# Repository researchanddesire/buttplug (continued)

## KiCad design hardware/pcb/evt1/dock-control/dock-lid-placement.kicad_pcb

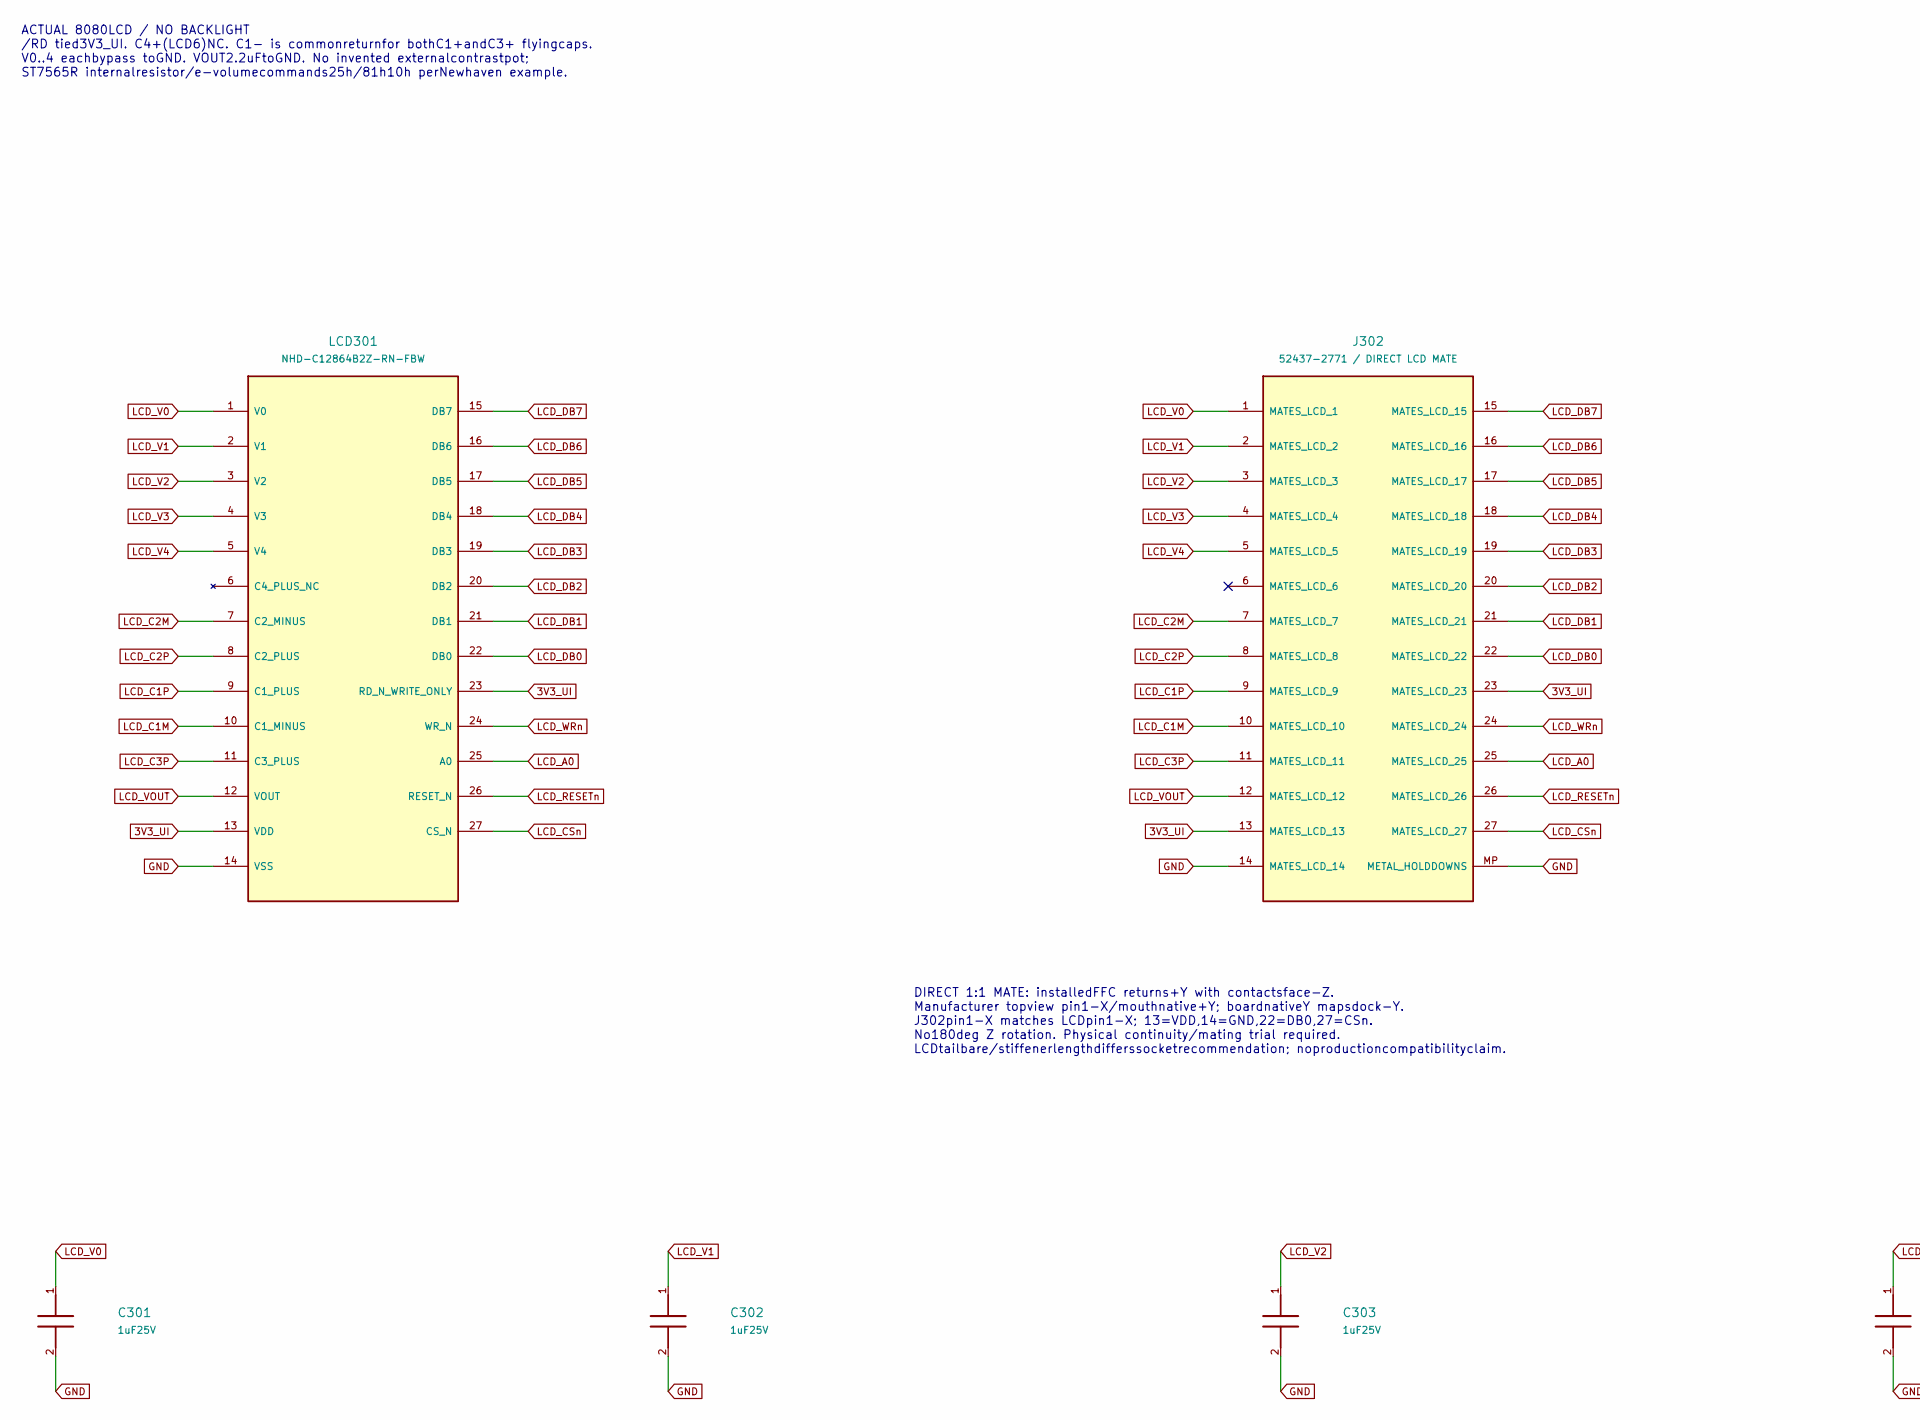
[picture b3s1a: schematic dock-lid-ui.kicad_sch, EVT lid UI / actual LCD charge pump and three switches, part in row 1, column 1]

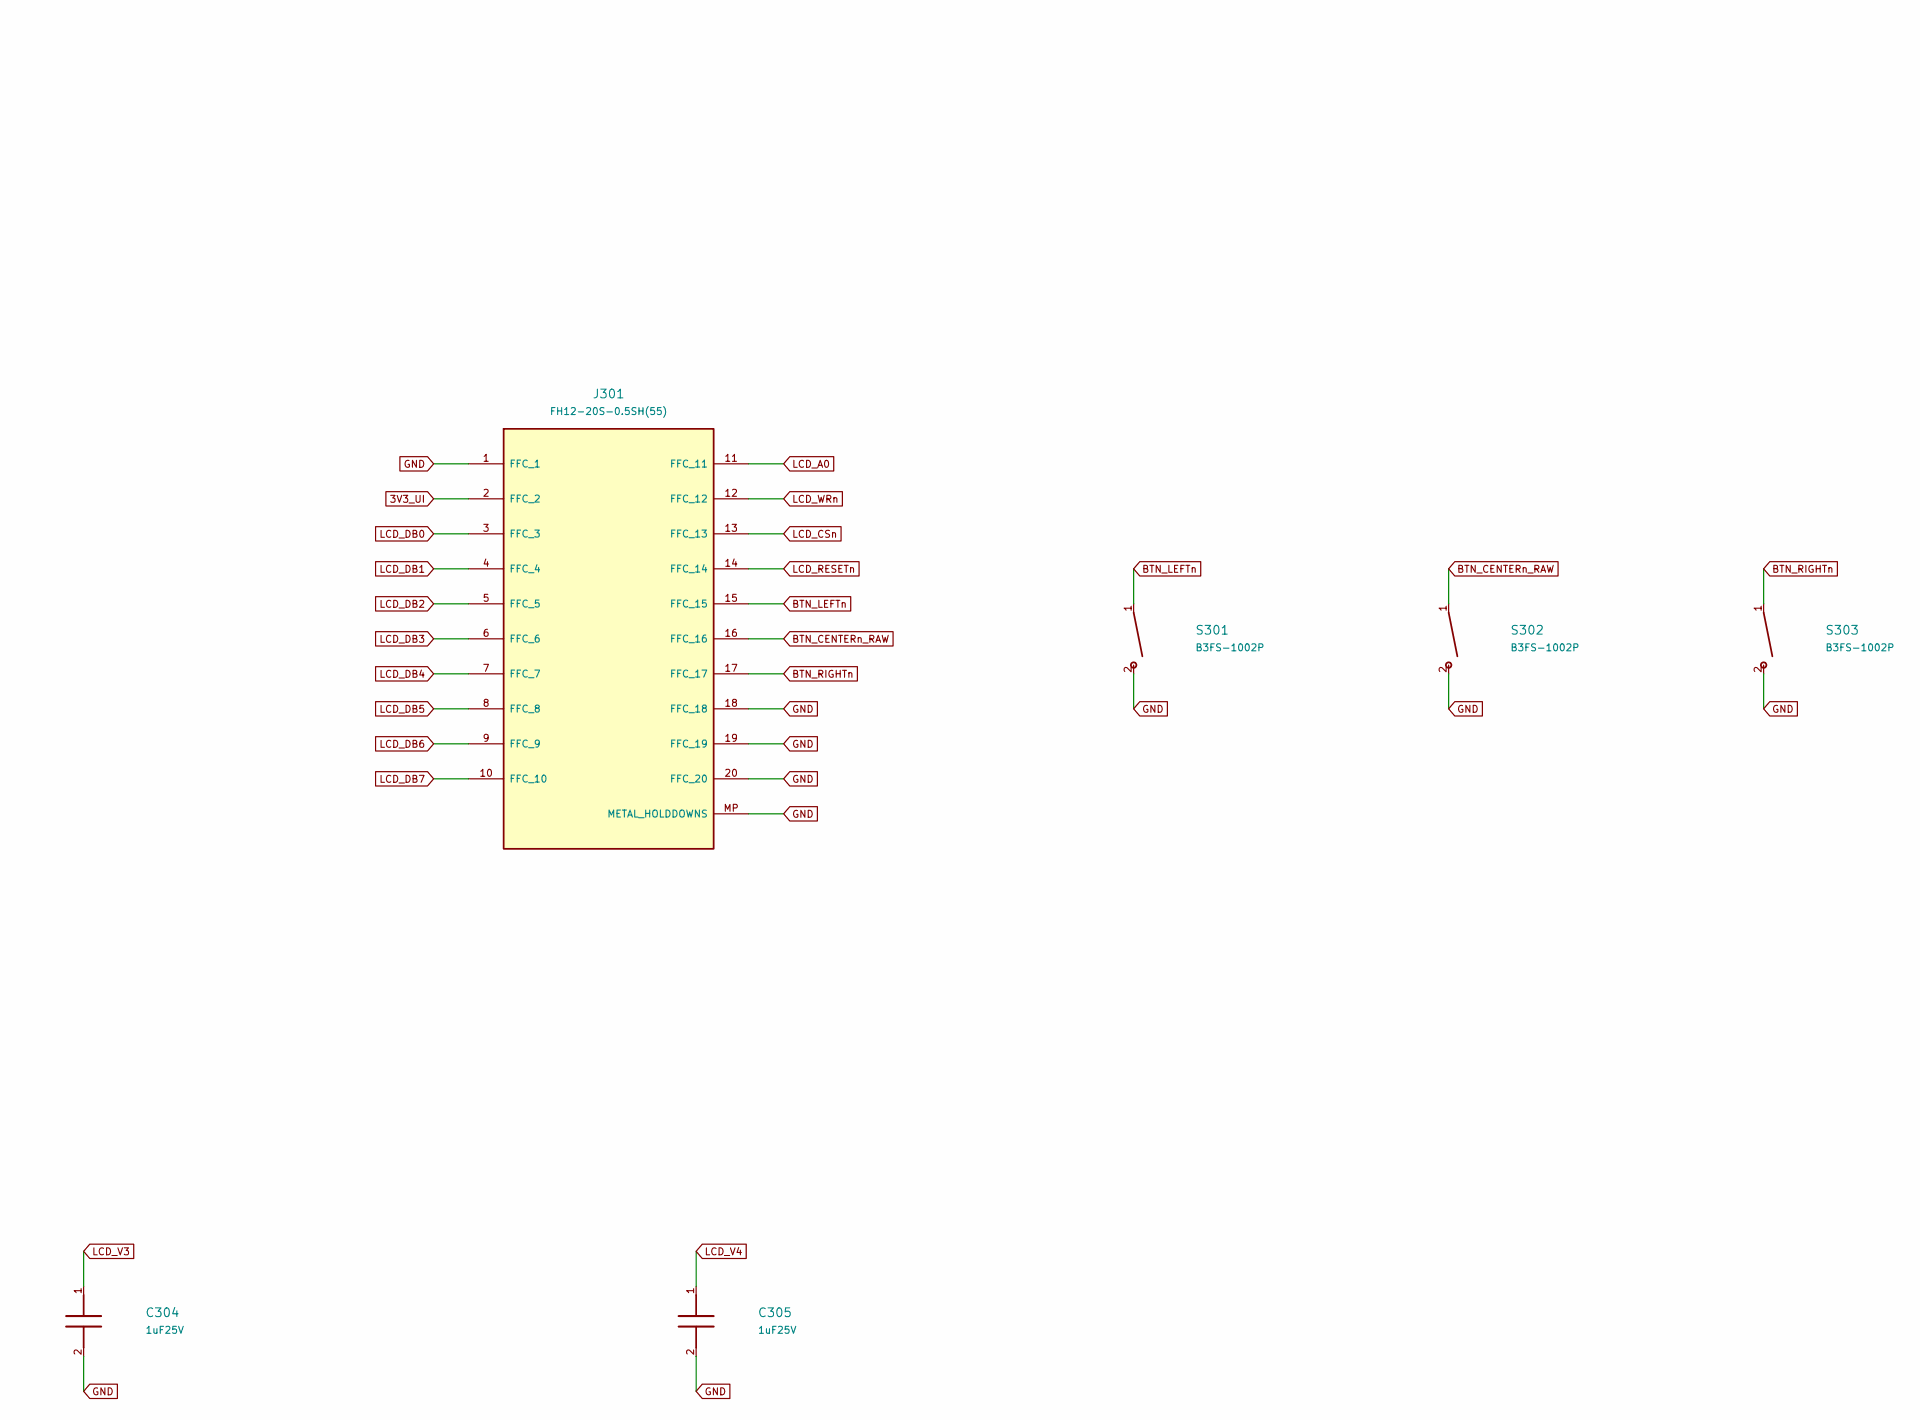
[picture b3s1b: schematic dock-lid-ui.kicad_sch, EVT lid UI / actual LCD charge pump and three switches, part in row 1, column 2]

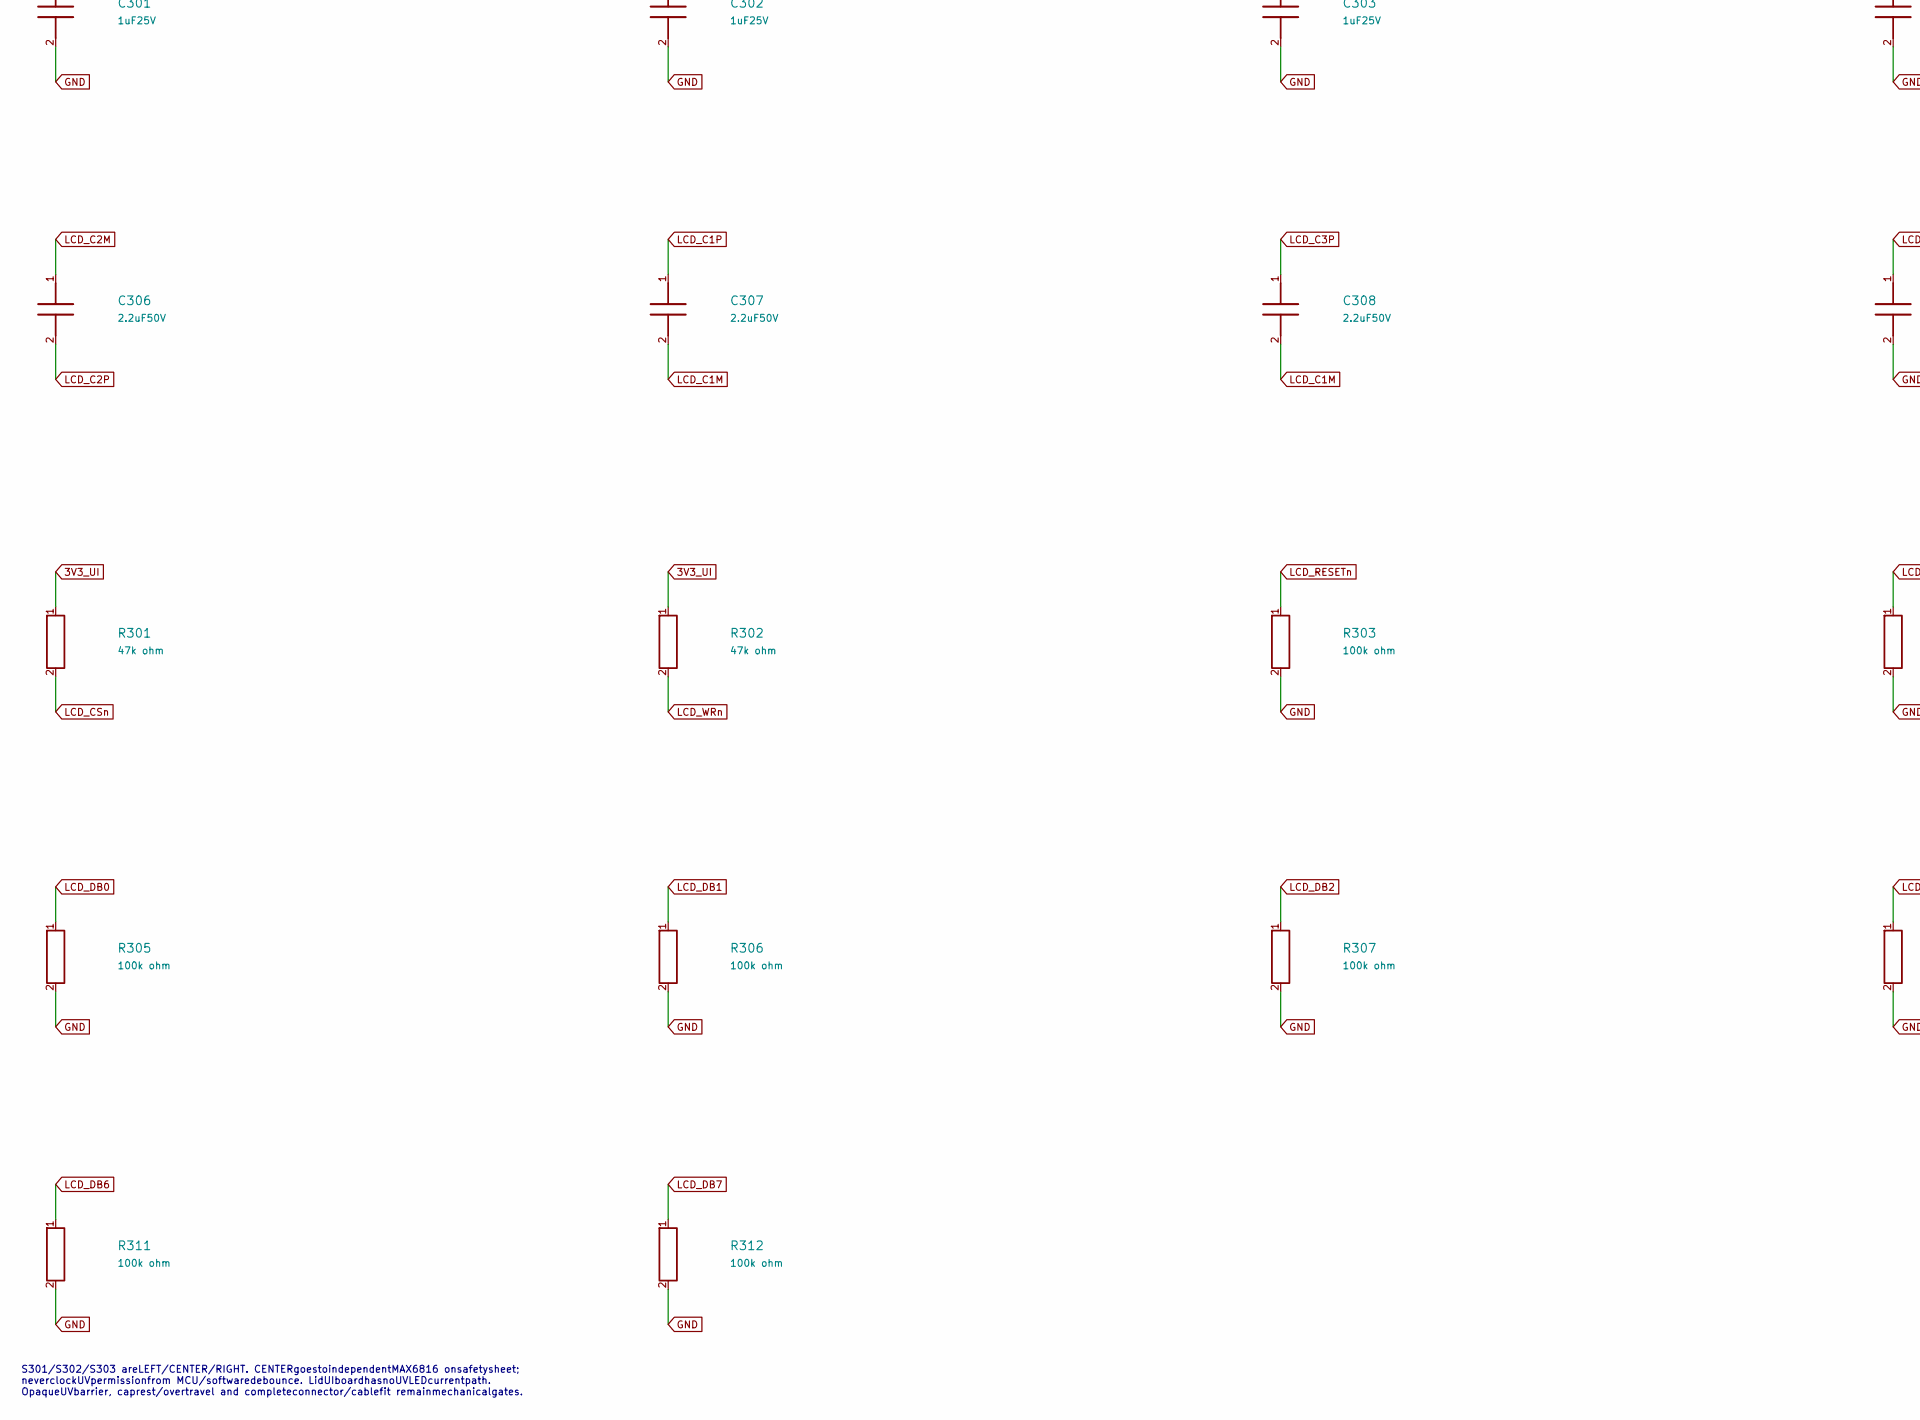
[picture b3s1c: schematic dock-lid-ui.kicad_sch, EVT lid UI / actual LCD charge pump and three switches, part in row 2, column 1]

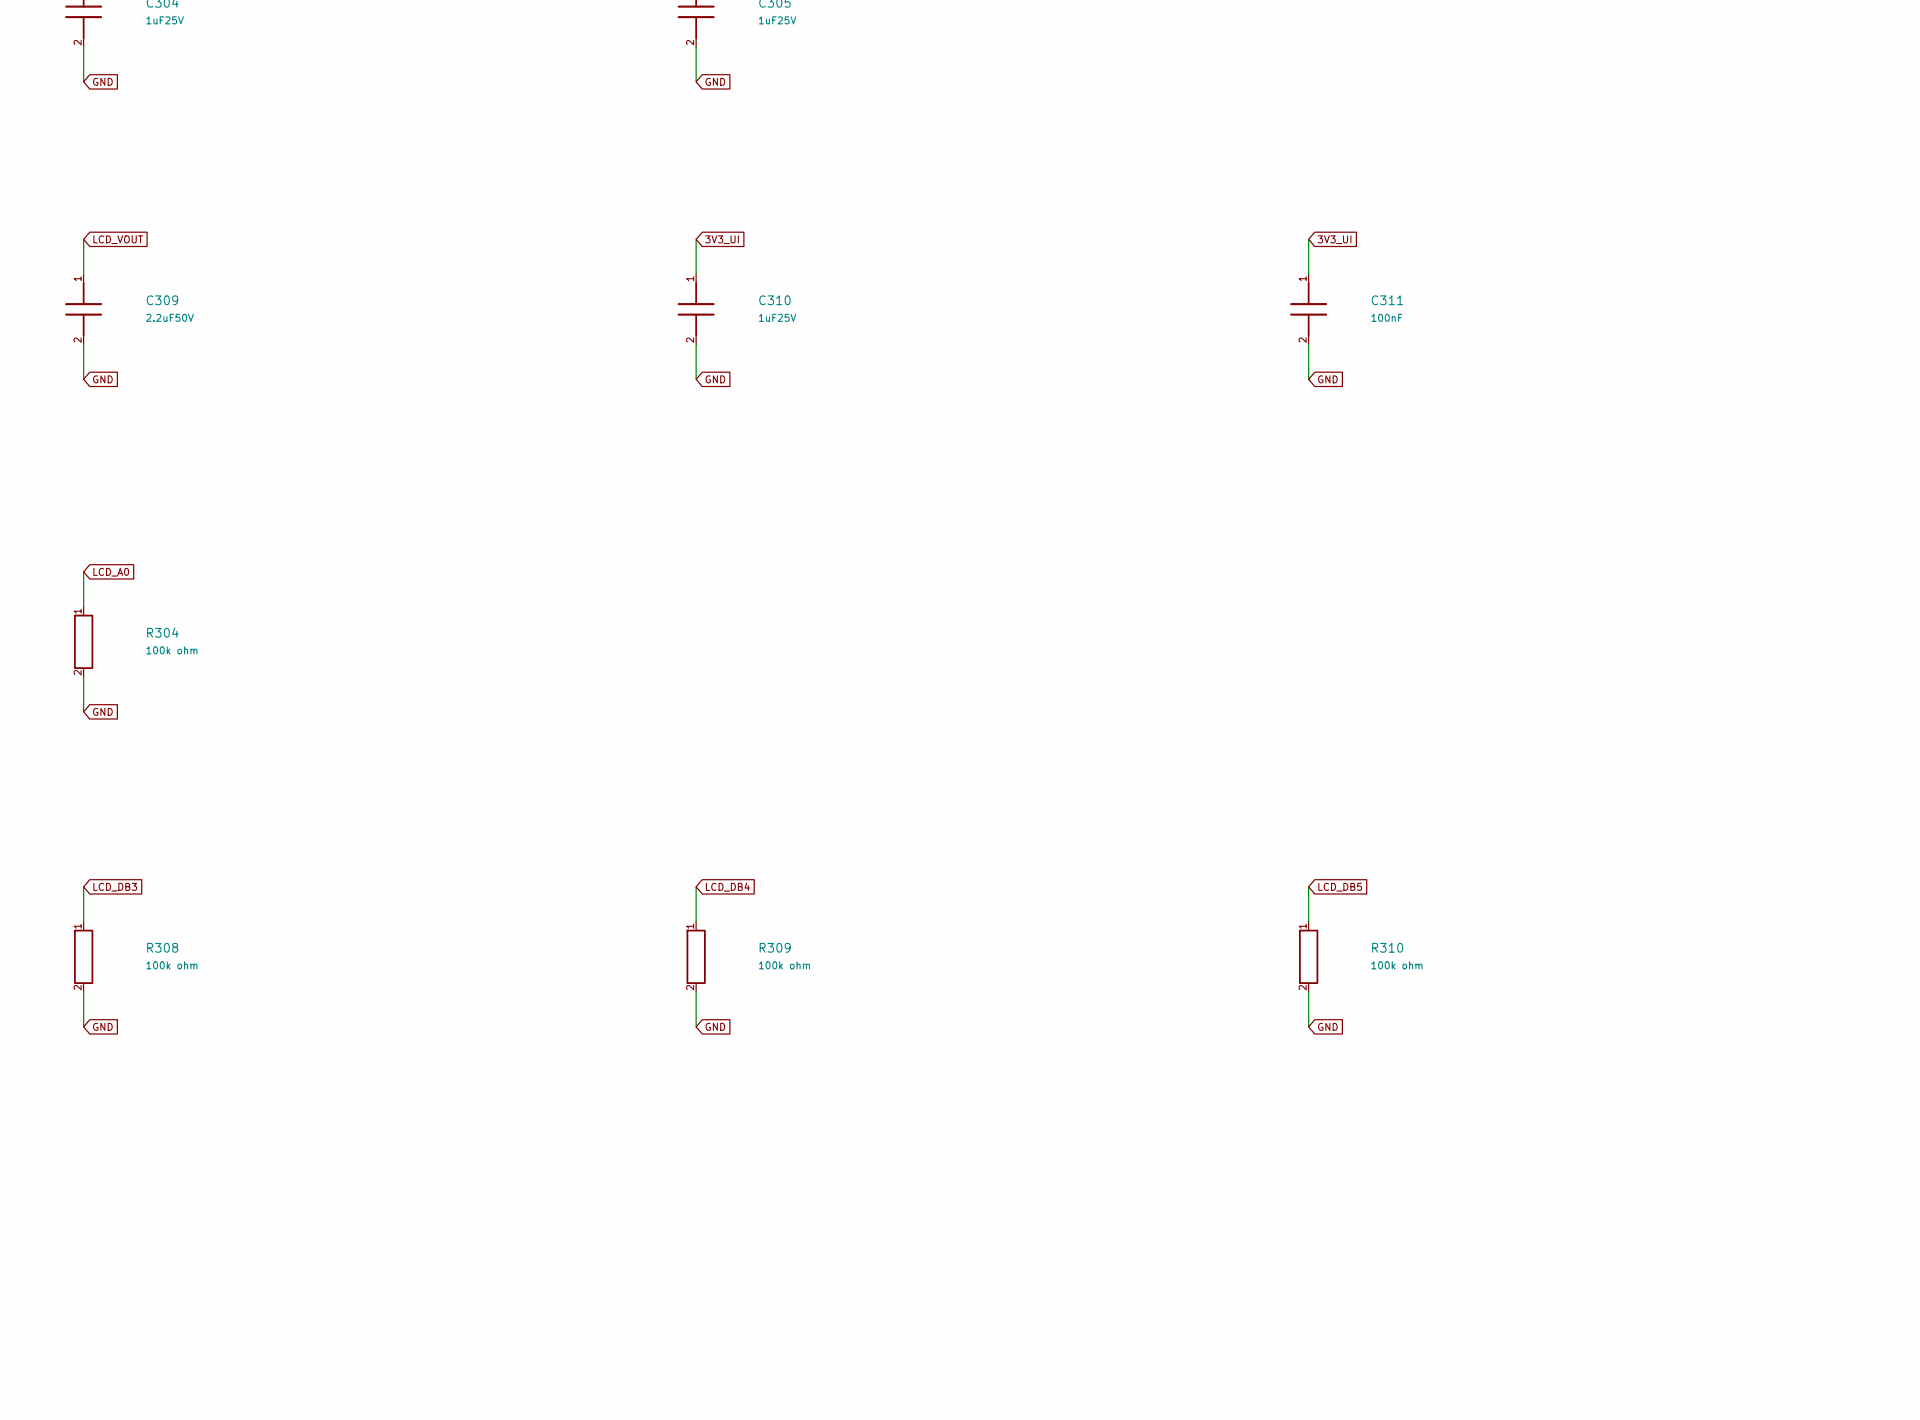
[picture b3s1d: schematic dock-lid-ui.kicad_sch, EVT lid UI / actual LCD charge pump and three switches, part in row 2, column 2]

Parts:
C301, C302, C303, C304, C305, C310: 1uF25V; C_0603_1608Metric; MPN C1608X7R1E105K080AB
C306, C307, C308, C309: 2.2uF50V; C_1206_3216Metric; MPN C3216X7R1H225K160AB
C311: 100nF; C_0402_1005Metric; MPN GRM155R71C104KA88D
J301: FH12-20S-0.5SH(55); Hirose_FH12-20S-0.5SH_1x20-1MP_P0.50mm_Horizontal; MPN FH12-20S-0.5SH(55)
J302: 52437-2771 / DIRECT LCD MATE; Molex_52437-2771_1x27-1MP_P0.50mm_Horizontal; MPN 52437-2771
LCD301: NHD-C12864B2Z-RN-FBW; MPN NHD-C12864B2Z-RN-FBW
R301, R302: 47k ohm; R_0603_1608Metric; MPN RC0603FR-0747KL
R303, R304, R305, R306, R307, R308, R309, R310, R311, R312: 100k ohm; R_0603_1608Metric; MPN RC0603FR-07100KL
S301, S302, S303: B3FS-1002P; SW_SPST_Omron_B3FS-100xP; MPN B3FS-1002P

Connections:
3V3_UI: C310.1, C311.1, J301.2 (FFC_2), J302.13 (MATES_LCD_13), J302.23 (MATES_LCD_23), LCD301.13 (VDD), LCD301.23 (RD_N_WRITE_ONLY), R301.1, R302.1
BTN_CENTERn_RAW: J301.16 (FFC_16), S302.1
BTN_LEFTn: J301.15 (FFC_15), S301.1
BTN_RIGHTn: J301.17 (FFC_17), S303.1
GND: C301.2, C302.2, C303.2, C304.2, C305.2, C309.2, C310.2, C311.2, J301.1 (FFC_1), J301.18 (FFC_18), J301.19 (FFC_19), J301.20 (FFC_20), J301.MP (METAL_HOLDDOWNS), J302.14 (MATES_LCD_14), J302.MP (METAL_HOLDDOWNS), LCD301.14 (VSS), R303.2, R304.2, R305.2, R306.2, R307.2, R308.2, R309.2, R310.2, R311.2, R312.2, S301.2, S302.2, S303.2
LCD_A0: J301.11 (FFC_11), J302.25 (MATES_LCD_25), LCD301.25 (A0), R304.1
LCD_C1M: C307.2, C308.2, J302.10 (MATES_LCD_10), LCD301.10 (C1_MINUS)
LCD_C1P: C307.1, J302.9 (MATES_LCD_9), LCD301.9 (C1_PLUS)
LCD_C2M: C306.1, J302.7 (MATES_LCD_7), LCD301.7 (C2_MINUS)
LCD_C2P: C306.2, J302.8 (MATES_LCD_8), LCD301.8 (C2_PLUS)
LCD_C3P: C308.1, J302.11 (MATES_LCD_11), LCD301.11 (C3_PLUS)
LCD_CSn: J301.13 (FFC_13), J302.27 (MATES_LCD_27), LCD301.27 (CS_N), R301.2
LCD_DB0: J301.3 (FFC_3), J302.22 (MATES_LCD_22), LCD301.22 (DB0), R305.1
LCD_DB1: J301.4 (FFC_4), J302.21 (MATES_LCD_21), LCD301.21 (DB1), R306.1
LCD_DB2: J301.5 (FFC_5), J302.20 (MATES_LCD_20), LCD301.20 (DB2), R307.1
LCD_DB3: J301.6 (FFC_6), J302.19 (MATES_LCD_19), LCD301.19 (DB3), R308.1
LCD_DB4: J301.7 (FFC_7), J302.18 (MATES_LCD_18), LCD301.18 (DB4), R309.1
LCD_DB5: J301.8 (FFC_8), J302.17 (MATES_LCD_17), LCD301.17 (DB5), R310.1
LCD_DB6: J301.9 (FFC_9), J302.16 (MATES_LCD_16), LCD301.16 (DB6), R311.1
LCD_DB7: J301.10 (FFC_10), J302.15 (MATES_LCD_15), LCD301.15 (DB7), R312.1
LCD_RESETn: J301.14 (FFC_14), J302.26 (MATES_LCD_26), LCD301.26 (RESET_N), R303.1
LCD_V0: C301.1, J302.1 (MATES_LCD_1), LCD301.1 (V0)
LCD_V1: C302.1, J302.2 (MATES_LCD_2), LCD301.2 (V1)
LCD_V2: C303.1, J302.3 (MATES_LCD_3), LCD301.3 (V2)
LCD_V3: C304.1, J302.4 (MATES_LCD_4), LCD301.4 (V3)
LCD_V4: C305.1, J302.5 (MATES_LCD_5), LCD301.5 (V4)
LCD_VOUT: C309.1, J302.12 (MATES_LCD_12), LCD301.12 (VOUT)
LCD_WRn: J301.12 (FFC_12), J302.24 (MATES_LCD_24), LCD301.24 (WR_N), R302.2

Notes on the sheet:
ACTUAL 8080LCD / NO BACKLIGHT /RD tied3V3_UI. C4+(LCD6)NC. C1- is commonreturnfor bothC1+andC3+ flyingcaps. V0..4 eachbypass toGND. VOUT2.2uFtoGND. No invented externalcontrastpot; ST7565R internalresistor/e-volumecommands25h/81h10h perNewhaven example.
DIRECT 1:1 MATE: installedFFC returns+Y with contactsface-Z. Manufacturer topview pin1-X/mouthnative+Y; boardnativeY mapsdock-Y. J302pin1-X matches LCDpin1-X; 13=VDD,14=GND,22=DB0,27=CSn. No180deg Z rotation. Physical continuity/mating trial required. LCDtailbare/stiffenerlengthdifferssocketrecomme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
S301/S302/S303 areLEFT/CENTER/RIGHT. CENTERgoestoindependentMAX6816 onsafetysheet; neverclockUVpermissionfrom MCU/softwaredebounce. LidUIboardhasnoUVLEDcurrentpath. OpaqueUVbarrier, caprest/overtravel and completeconnector/cablefit remainmechanicalgates.

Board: 2 copper layers, 28 parts (0 on the bottom side), 28 nets, no tracks yet.

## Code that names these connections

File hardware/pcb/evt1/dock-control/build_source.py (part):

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LCD_PINS.update({15+i:('DB'+str(7-i),'LCD_DB'+str(7-i))for i in range(8)})
LCD_PINS.update({23:('RD_N_WRITE_ONLY','3V3_UI'),24:('WR_N','LCD_WRn'),25:('A0','LCD_A0'),26:('RESET_N','LCD_RESETn'),27:('CS_N','LCD_CSn')})
def lcd_kind(i):return 'no_connect'if i==6 else('power_in'if i in(13,14)else('input'if i>=15 else'passive'))
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g.ic('BASE_CONTEXT_PORTS',[(i+1,n,'passive')for i,n in enumerate(CONTEXT_NETS[:12])],[(i+13,n,'passive')for i,n in enumerate(CONTEXT_NETS[12:])],'','Standalone intersheet context only; not purchased/PCBhardware. Remove when combining real sibling circuits.')
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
